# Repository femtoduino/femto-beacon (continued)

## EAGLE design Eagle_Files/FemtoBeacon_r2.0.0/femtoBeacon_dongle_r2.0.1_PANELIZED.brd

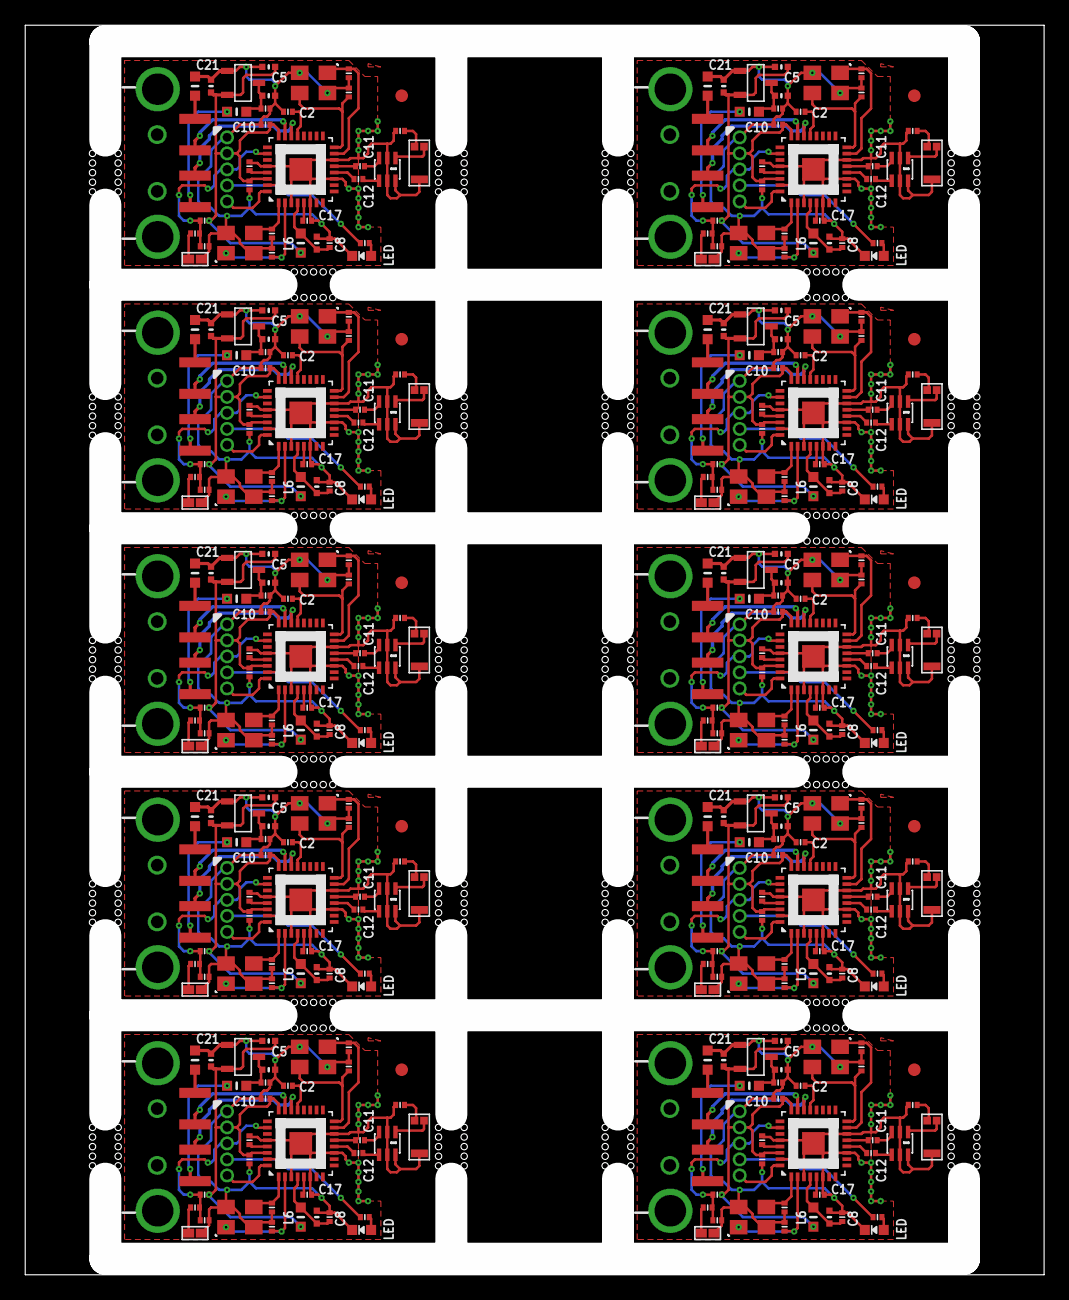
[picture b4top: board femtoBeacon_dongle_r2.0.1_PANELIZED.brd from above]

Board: 2 copper layers, 80.8 x 99.1 mm, 360 parts (0 on the bottom side), 260 nets.

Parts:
ANT1, ANT2, ANT3, ANT4, ANT5, ANT6, ANT7, ANT8, ANT9, ANT10: PULSE_ANT_2.4GHZ; ANT_BAR
BTN, BTN1, BTN2, BTN3, BTN4, BTN5, BTN6, BTN7, BTN8, BTN9: DNP; SPST_SMD
C1, C2, C8, C9, C10, C16, C17, C18, C19, C27, C28, C29, C37, C38, C39, C40, C46, C47, C48, C56, C57, C58, C59, C65, C66, C67, C75, C76, C77, C78, C84, C85, C86, C94, C95, C96, C97, C103, C104, C105, C113, C114, C115, C116, C122, C123, C124, C132, C133, C134, C135, C141, C142, C143, C151, C152, C153, C154, C160, C161, C162, C170, C171, C172, C173, C179, C180, C181, C189, C190: 0.1uF; PART
C3, C4, C32, C33, C51, C52, C70, C71, C89, C90, C108, C109, C127, C128, C146, C147, C165, C166, C184, C185: 10pF; PART
C5, C6, C34, C35, C53, C54, C72, C73, C91, C92, C110, C111, C129, C130, C148, C149, C167, C168, C186, C187: 2.2uF; _0402MP
C7, C36, C55, C74, C93, C112, C131, C150, C169, C188: 0.47uF; PART
C11, C12, C20, C23, C41, C42, C60, C61, C79, C80, C98, C99, C117, C118, C136, C137, C155, C156, C174, C175: 22pF, C0G, 5%; PART
C13, C24, C43, C62, C81, C100, C119, C138, C157, C176: DNP; PART
C14, C15, C25, C26, C44, C45, C63, C64, C82, C83, C101, C102, C120, C121, C139, C140, C158, C159, C177, C178: 9pF; PART
C21, C22, C30, C31, C49, C50, C68, C69, C87, C88, C106, C107, C125, C126, C144, C145, C163, C164, C182, C183: 10uF; _0402MP
CN1, CN2, CN3, CN4, CN5, CN6, CN7, CN8, CN9, CN10: USB_A-SMT
FB1, FB2, FB3, FB4, FB5, FB6, FB7, FB8, FB9, FB10, FB11, FB12, FB13, FB14, FB15, FB16, FB17, FB18, FB19, FB20: _0603MP
FID1, FID2, FID3, FID4, FID5, FID6, FID7, FID8, FID9, FID10: FIDUCIAL; FIDUCIAL_1MM
L1, L2, L3, L4, L5, L6, L7, L8, L9, L10: 10uH; _0603MP
LDO_VREG, LDO_VREG1, LDO_VREG2, LDO_VREG3, LDO_VREG4, LDO_VREG5, LDO_VREG6, LDO_VREG7, LDO_VREG8, LDO_VREG9: MCP1700T-3302E/TT
LED, LED1, LED2, LED3, LED4, LED5, LED6, LED7, LED8, LED9: BLUE; CHIPLED_0603_NOOUTLINE
R1, R3, R4, R6, R7, R9, R10, R12, R13, R15, R16, R18, R19, R21, R22, R24, R25, R27, R28, R30: 330; PART
R2, R5, R8, R11, R14, R17, R20, R23, R26, R29: 10K; PART
U$1, U$4, U$7, U$10, U$14, U$17, U$20, U$23, U$26, U$29: 1X5_ROUND
U$2, U$5, U$8, U$11, U$12, U$15, U$18, U$21, U$24, U$27: JOHANSON_2450BM15A0015E; 0805_BALUN
U$3, U$6, U$9, U$13, U$16, U$19, U$22, U$25, U$28, U$76: ATSAMR21E18A-MUT; QFN32
XOSC, XOSC1, XOSC2, XOSC3, XOSC4, XOSC5, XOSC6, XOSC7, XOSC8, XOSC9: 12MHz; TSX-3225
XOSCRF, XOSCRF1, XOSCRF2, XOSCRF3, XOSCRF4, XOSCRF5, XOSCRF6, XOSCRF7, XOSCRF8, XOSCRF9: 16MHz; TSX-3225

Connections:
3.3V: C5.1, C10.1, C16.1, C21.2, L6.1, LDO_VREG.VOUT, R2.2, U$1.P$2, U$76.24, U$76.30
3.3V1: C19.1, C27.1, C30.2, C34.1, L1.1, LDO_VREG1.VOUT, R5.2, U$3.24, U$3.30, U$4.P$2
3.3V2: C40.1, C46.1, C49.2, C53.1, L2.1, LDO_VREG2.VOUT, R8.2, U$6.24, U$6.30, U$7.P$2
3.3V3: C59.1, C65.1, C68.2, C72.1, L3.1, LDO_VREG3.VOUT, R11.2, U$9.24, U$9.30, U$10.P$2
3.3V4: C78.1, C84.1, C87.2, C91.1, L4.1, LDO_VREG4.VOUT, R14.2, U$13.24, U$13.30, U$14.P$2
3.3V5: C97.1, C103.1, C106.2, C110.1, L5.1, LDO_VREG5.VOUT, R17.2, U$16.24, U$16.30, U$17.P$2
3.3V6: C116.1, C122.1, C125.2, C129.1, L7.1, LDO_VREG6.VOUT, R20.2, U$19.24, U$19.30, U$20.P$2
3.3V7: C135.1, C141.1, C144.2, C148.1, L8.1, LDO_VREG7.VOUT, R23.2, U$22.24, U$22.30, U$23.P$2
3.3V8: C154.1, C160.1, C163.2, C167.1, L9.1, LDO_VREG8.VOUT, R26.2, U$25.24, U$25.30, U$26.P$2
3.3V9: C173.1, C179.1, C182.2, C186.1, L10.1, LDO_VREG9.VOUT, R29.2, U$28.24, U$28.30, U$29.P$2
ANT_OUT: ANT1.1, U$12.1
ANT_OUT1: ANT2.1, U$2.1
ANT_OUT2: ANT3.1, U$5.1
ANT_OUT3: ANT4.1, U$8.1
ANT_OUT4: ANT5.1, U$11.1
ANT_OUT5: ANT6.1, U$15.1
ANT_OUT6: ANT7.1, U$18.1
ANT_OUT7: ANT8.1, U$21.1
ANT_OUT8: ANT9.1, U$24.1
ANT_OUT9: ANT10.1, U$27.1
AVDD: C17.1, U$76.5
AVDD1: C28.1, U$3.5
AVDD2: C47.1, U$6.5
AVDD3: C66.1, U$9.5
AVDD4: C85.1, U$13.5
AVDD5: C104.1, U$16.5
AVDD6: C123.1, U$19.5
AVDD7: C142.1, U$22.5
AVDD8: C161.1, U$25.5
AVDD9: C180.1, U$28.5
DVDD: C2.1, U$76.21
DVDD1: C29.1, U$3.21
DVDD2: C48.1, U$6.21
DVDD3: C67.1, U$9.21
DVDD4: C86.1, U$13.21
DVDD5: C105.1, U$16.21
DVDD6: C124.1, U$19.21
DVDD7: C143.1, U$22.21
DVDD8: C162.1, U$25.21
DVDD9: C181.1, U$28.21
GND: ANT1.3, BTN.2, C1.2, C2.2, C3.1, C4.2, C5.2, C6.2, C7.2, C8.2, C9.2, C10.2, C13.2, C14.1, C15.2, C16.2, C17.2, C21.1, C22.1, FB1.2, LDO_VREG.GND, LED.C, U$1.P$1, U$12.2, U$12.5, U$12.6, U$76.3, U$76.6, U$76.11, U$76.14, U$76.28, U$76.33, XOSC.2, XOSC.4, XOSCRF.2, XOSCRF.4
GND1: ANT2.3, BTN1.2, C18.2, C19.2, C24.2, C25.1, C26.2, C27.2, C28.2, C29.2, C30.1, C31.1, C32.1, C33.2, C34.2, C35.2, C36.2, C37.2, C38.2, FB3.2, LDO_VREG1.GND, LED1.C, U$2.2, U$2.5, U$2.6, U$3.3, U$3.6, U$3.11, U$3.14, U$3.28, U$3.33, U$4.P$1, XOSC1.2, XOSC1.4, XOSCRF1.2, XOSCRF1.4
GND2: ANT3.3, BTN2.2, C39.2, C40.2, C43.2, C44.1, C45.2, C46.2, C47.2, C48.2, C49.1, C50.1, C51.1, C52.2, C53.2, C54.2, C55.2, C56.2, C57.2, FB5.2, LDO_VREG2.GND, LED2.C, U$5.2, U$5.5, U$5.6, U$6.3, U$6.6, U$6.11, U$6.14, U$6.28, U$6.33, U$7.P$1, XOSC2.2, XOSC2.4, XOSCRF2.2, XOSCRF2.4
GND3: ANT4.3, BTN3.2, C58.2, C59.2, C62.2, C63.1, C64.2, C65.2, C66.2, C67.2, C68.1, C69.1, C70.1, C71.2, C72.2, C73.2, C74.2, C75.2, C76.2, FB7.2, LDO_VREG3.GND, LED3.C, U$8.2, U$8.5, U$8.6, U$9.3, U$9.6, U$9.11, U$9.14, U$9.28, U$9.33, U$10.P$1, XOSC3.2, XOSC3.4, XOSCRF3.2, XOSCRF3.4
GND4: ANT5.3, BTN4.2, C77.2, C78.2, C81.2, C82.1, C83.2, C84.2, C85.2, C86.2, C87.1, C88.1, C89.1, C90.2, C91.2, C92.2, C93.2, C94.2, C95.2, FB9.2, LDO_VREG4.GND, LED4.C, U$11.2, U$11.5, U$11.6, U$13.3, U$13.6, U$13.11, U$13.14, U$13.28, U$13.33, U$14.P$1, XOSC4.2, XOSC4.4, XOSCRF4.2, XOSCRF4.4
GND5: ANT6.3, BTN5.2, C96.2, C97.2, C100.2, C101.1, C102.2, C103.2, C104.2, C105.2, C106.1, C107.1, C108.1, C109.2, C110.2, C111.2, C112.2, C113.2, C114.2, FB11.2, LDO_VREG5.GND, LED5.C, U$15.2, U$15.5, U$15.6, U$16.3, U$16.6, U$16.11, U$16.14, U$16.28, U$16.33, U$17.P$1, XOSC5.2, XOSC5.4, XOSCRF5.2, XOSCRF5.4
GND6: ANT7.3, BTN6.2, C115.2, C116.2, C119.2, C120.1, C121.2, C122.2, C123.2, C124.2, C125.1, C126.1, C127.1, C128.2, C129.2, C130.2, C131.2, C132.2, C133.2, FB13.2, LDO_VREG6.GND, LED6.C, U$18.2, U$18.5, U$18.6, U$19.3, U$19.6, U$19.11, U$19.14, U$19.28, U$19.33, U$20.P$1, XOSC6.2, XOSC6.4, XOSCRF6.2, XOSCRF6.4
GND7: ANT8.3, BTN7.2, C134.2, C135.2, C138.2, C139.1, C140.2, C141.2, C142.2, C143.2, C144.1, C145.1, C146.1, C147.2, C148.2, C149.2, C150.2, C151.2, C152.2, FB15.2, LDO_VREG7.GND, LED7.C, U$21.2, U$21.5, U$21.6, U$22.3, U$22.6, U$22.11, U$22.14, U$22.28, U$22.33, U$23.P$1, XOSC7.2, XOSC7.4, XOSCRF7.2, XOSCRF7.4
GND8: ANT9.3, BTN8.2, C153.2, C154.2, C157.2, C158.1, C159.2, C160.2, C161.2, C162.2, C163.1, C164.1, C165.1, C166.2, C167.2, C168.2, C169.2, C170.2, C171.2, FB17.2, LDO_VREG8.GND, LED8.C, U$24.2, U$24.5, U$24.6, U$25.3, U$25.6, U$25.11, U$25.14, U$25.28, U$25.33, U$26.P$1, XOSC8.2, XOSC8.4, XOSCRF8.2, XOSCRF8.4
GND9: ANT10.3, BTN9.2, C172.2, C173.2, C176.2, C177.1, C178.2, C179.2, C180.2, C181.2, C182.1, C183.1, C184.1, C185.2, C186.2, C187.2, C188.2, C189.2, C190.2, FB19.2, LDO_VREG9.GND, LED9.C, U$27.2, U$27.5, U$27.6, U$28.3, U$28.6, U$28.11, U$28.14, U$28.28, U$28.33, U$29.P$1, XOSC9.2, XOSC9.4, XOSCRF9.2, XOSCRF9.4
unnamed: C11.2, U$12.3
unnamed: ANT1.2, C13.1
unnamed: C12.2, U$12.4
unnamed: CN1.VBUS, FB2.1
unnamed: CN1.GND, FB1.1
unnamed: BTN1.1, R3.1
unnamed: LED1.A, R6.2
unnamed: C20.2, U$2.3
unnamed: LED.A, R4.2
unnamed: C23.2, U$2.4
unnamed: ANT2.2, C24.1
unnamed: CN2.GND, FB3.1
unnamed: CN2.VBUS, FB4.1
unnamed: BTN2.1, R7.1
unnamed: LED2.A, R9.2
unnamed: C41.2, U$5.3
unnamed: C42.2, U$5.4
unnamed: BTN.1, R1.1
unnamed: ANT3.2, C43.1
unnamed: CN3.GND, FB5.1
unnamed: CN3.VBUS, FB6.1
unnamed: BTN3.1, R10.1
unnamed: LED3.A, R12.2
unnamed: C60.2, U$8.3
unnamed: C61.2, U$8.4
unnamed: ANT4.2, C62.1
unnamed: CN4.GND, FB7.1
unnamed: CN4.VBUS, FB8.1
unnamed: BTN4.1, R13.1
unnamed: LED4.A, R15.2
unnamed: C79.2, U$11.3
unnamed: C80.2, U$11.4
unnamed: ANT5.2, C81.1
unnamed: CN5.GND, FB9.1
unnamed: CN5.VBUS, FB10.1
unnamed: BTN5.1, R16.1
unnamed: LED5.A, R18.2
unnamed: C98.2, U$15.3
unnamed: C99.2, U$15.4
unnamed: ANT6.2, C100.1
unnamed: CN6.GND, FB11.1
unnamed: CN6.VBUS, FB12.1
unnamed: BTN6.1, R19.1
unnamed: LED6.A, R21.2
unnamed: C117.2, U$18.3
unnamed: C118.2, U$18.4
unnamed: ANT7.2, C119.1
unnamed: CN7.GND, FB13.1
unnamed: CN7.VBUS, FB14.1
unnamed: BTN7.1, R22.1
unnamed: LED7.A, R24.2
unnamed: C136.2, U$21.3
unnamed: C137.2, U$21.4
unnamed: ANT8.2, C138.1
unnamed: CN8.GND, FB15.1
unnamed: CN8.VBUS, FB16.1
unnamed: BTN8.1, R25.1
unnamed: LED8.A, R27.2
unnamed: C155.2, U$24.3
unnamed: C156.2, U$24.4
unnamed: ANT9.2, C157.1
unnamed: CN9.GND, FB17.1
unnamed: CN9.VBUS, FB18.1
unnamed: BTN9.1, R28.1
unnamed: LED9.A, R30.2
unnamed: C174.2, U$27.3
unnamed: C175.2, U$27.4
unnamed: ANT10.2, C176.1
unnamed: CN10.GND, FB19.1
unnamed: CN10.VBUS, FB20.1
PA14/XIN_MC/RX: C3.2, U$76.15, XOSC.1
PA14/XIN_MC/RX1: C32.2, U$3.15, XOSC1.1
PA14/XIN_MC/RX2: C51.2, U$6.15, XOSC2.1
PA14/XIN_MC/RX3: C70.2, U$9.15, XOSC3.1
PA14/XIN_MC/RX4: C89.2, U$13.15, XOSC4.1
PA14/XIN_MC/RX5: C108.2, U$16.15, XOSC5.1
PA14/XIN_MC/RX6: C127.2, U$19.15, XOSC6.1
PA14/XIN_MC/RX7: C146.2, U$22.15, XOSC7.1
PA14/XIN_MC/RX8: C165.2, U$25.15, XOSC8.1
PA14/XIN_MC/RX9: C184.2, U$28.15, XOSC9.1
PA15/XOUT_MC/TX: C4.1, U$76.16, XOSC.3
PA15/XOUT_MC/TX1: C33.1, U$3.16, XOSC1.3
PA15/XOUT_MC/TX2: C52.1, U$6.16, XOSC2.3
PA15/XOUT_MC/TX3: C71.1, U$9.16, XOSC3.3
PA15/XOUT_MC/TX4: C90.1, U$13.16, XOSC4.3
PA15/XOUT_MC/TX5: C109.1, U$16.16, XOSC5.3
PA15/XOUT_MC/TX6: C128.1, U$19.16, XOSC6.3
PA15/XOUT_MC/TX7: C147.1, U$22.16, XOSC7.3
PA15/XOUT_MC/TX8: C166.1, U$25.16, XOSC8.3
PA15/XOUT_MC/TX9: C185.1, U$28.16, XOSC9.3
PA24/USBDM: CN1.D-, U$76.22
PA24/USBDM1: CN2.D-, U$3.22
PA24/USBDM2: CN3.D-, U$6.22
PA24/USBDM3: CN4.D-, U$9.22
PA24/USBDM4: CN5.D-, U$13.22
PA24/USBDM5: CN6.D-, U$16.22
PA24/USBDM6: CN7.D-, U$19.22
PA24/USBDM7: CN8.D-, U$22.22
PA24/USBDM8: CN9.D-, U$25.22
PA24/USBDM9: CN10.D-, U$28.22
PA25/USBDP: CN1.D+, U$76.23
PA25/USBDP1: CN2.D+, U$3.23
PA25/USBDP2: CN3.D+, U$6.23
PA25/USBDP3: CN4.D+, U$9.23
PA25/USBDP4: CN5.D+, U$13.23
PA25/USBDP5: CN6.D+, U$16.23
PA25/USBDP6: CN7.D+, U$19.23
PA25/USBDP7: CN8.D+, U$22.23
PA25/USBDP8: CN9.D+, U$25.23
PA25/USBDP9: CN10.D+, U$28.23
PA30/SWCLK: R4.1, U$1.P$4, U$76.31
PA30/SWCLK1: R6.1, U$3.31, U$4.P$4
PA30/SWCLK2: R9.1, U$6.31, U$7.P$4
PA30/SWCLK3: R12.1, U$9.31, U$10.P$4
PA30/SWCLK4: R15.1, U$13.31, U$14.P$4
PA30/SWCLK5: R18.1, U$16.31, U$17.P$4
PA30/SWCLK6: R21.1, U$19.31, U$20.P$4
PA30/SWCLK7: R24.1, U$22.31, U$23.P$4
PA30/SWCLK8: R27.1, U$25.31, U$26.P$4
PA30/SWCLK9: R30.1, U$28.31, U$29.P$4
PA31/SWDIO: U$1.P$5, U$76.32
PA31/SWDIO1: U$3.32, U$4.P$5
PA31/SWDIO2: U$6.32, U$7.P$5
PA31/SWDIO3: U$9.32, U$10.P$5
PA31/SWDIO4: U$13.32, U$14.P$5
PA31/SWDIO5: U$16.32, U$17.P$5
PA31/SWDIO6: U$19.32, U$20.P$5
PA31/SWDIO7: U$22.32, U$23.P$5
PA31/SWDIO8: U$25.32, U$26.P$5
PA31/SWDIO9: U$28.32, U$29.P$5
RESET: C1.1, R1.2, R2.1, U$1.P$3, U$76.26
RESET1: C18.1, R3.2, R5.1, U$3.26, U$4.P$3
RESET2: C39.1, R7.2, R8.1, U$6.26, U$7.P$3
RESET3: C58.1, R10.2, R11.1, U$9.26, U$10.P$3
RESET4: C77.1, R13.2, R14.1, U$13.26, U$14.P$3
RESET5: C96.1, R16.2, R17.1, U$16.26, U$17.P$3
RESET6: C115.1, R19.2, R20.1, U$19.26, U$20.P$3
RESET7: C134.1, R22.2, R23.1, U$22.26, U$23.P$3
RESET8: C153.1, R25.2, R26.1, U$25.26, U$26.P$3
RESET9: C172.1, R28.2, R29.1, U$28.26, U$29.P$3
RFN: C11.1, U$76.13
RFN1: C20.1, U$3.13
RFN2: C41.1, U$6.13
RFN3: C60.1, U$9.13
RFN4: C79.1, U$13.13
RFN5: C98.1, U$16.13
RFN6: C117.1, U$19.13
RFN7: C136.1, U$22.13
RFN8: C155.1, U$25.13
RFN9: C174.1, U$28.13
RFP: C12.1, U$76.12
RFP1: C23.1, U$3.12
RFP2: C42.1, U$6.12
RFP3: C61.1, U$9.12
RFP4: C80.1, U$13.12
RFP5: C99.1, U$16.12
RFP6: C118.1, U$19.12
RFP7: C137.1, U$22.12
RFP8: C156.1, U$25.12
RFP9: C175.1, U$28.12
VDDANA: C8.1, C22.2, L6.2, U$76.4
VDDANA1: C31.2, C37.1, L1.2, U$3.4
VDDANA2: C50.2, C56.1, L2.2, U$6.4
VDDANA3: C69.2, C75.1, L3.2, U$9.4
VDDANA4: C88.2, C94.1, L4.2, U$13.4
VDDANA5: C107.2, C113.1, L5.2, U$16.4
VDDANA6: C126.2, C132.1, L7.2, U$19.4
VDDANA7: C145.2, C151.1, L8.2, U$22.4
VDDANA8: C164.2, C170.1, L9.2, U$25.4
VDDANA9: C183.2, C189.1, L10.2, U$28.4
VDDCORE: C9.1, U$76.29
VDDCORE1: C38.1, U$3.29
VDDCORE2: C57.1, U$6.29
VDDCORE3: C76.1, U$9.29
VDDCORE4: C95.1, U$13.29
VDDCORE5: C114.1, U$16.29
VDDCORE6: C133.1, U$19.29
VDDCORE7: C152.1, U$22.29
VDDCORE8: C171.1, U$25.29
VDDCORE9: C190.1, U$28.29
VIN: C6.1, C7.1, FB2.2, LDO_VREG.VIN
VIN1: C35.1, C36.1, FB4.2, LDO_VREG1.VIN
VIN2: C54.1, C55.1, FB6.2, LDO_VREG2.VIN
VIN3: C73.1, C74.1, FB8.2, LDO_VREG3.VIN
VIN4: C92.1, C93.1, FB10.2, LDO_VREG4.VIN
VIN5: C111.1, C112.1, FB12.2, LDO_VREG5.VIN
VIN6: C130.1, C131.1, FB14.2, LDO_VREG6.VIN
VIN7: C149.1, C150.1, FB16.2, LDO_VREG7.VIN
VIN8: C168.1, C169.1, FB18.2, LDO_VREG8.VIN
VIN9: C187.1, C188.1, FB20.2, LDO_VREG9.VIN
XTALIN: C14.2, U$76.2, XOSCRF.1
XTALIN1: C25.2, U$3.2, XOSCRF1.1
XTALIN2: C44.2, U$6.2, XOSCRF2.1
XTALIN3: C63.2, U$9.2, XOSCRF3.1
XTALIN4: C82.2, U$13.2, XOSCRF4.1
XTALIN5: C101.2, U$16.2, XOSCRF5.1
XTALIN6: C120.2, U$19.2, XOSCRF6.1
XTALIN7: C139.2, U$22.2, XOSCRF7.1
XTALIN8: C158.2, U$25.2, XOSCRF8.1
XTALIN9: C177.2, U$28.2, XOSCRF9.1
XTALOUT: C15.1, U$76.1, XOSCRF.3
XTALOUT1: C26.1, U$3.1, XOSCRF1.3
XTALOUT2: C45.1, U$6.1, XOSCRF2.3
XTALOUT3: C64.1, U$9.1, XOSCRF3.3
XTALOUT4: C83.1, U$13.1, XOSCRF4.3
XTALOUT5: C102.1, U$16.1, XOSCRF5.3
XTALOUT6: C121.1, U$19.1, XOSCRF6.3
XTALOUT7: C140.1, U$22.1, XOSCRF7.3
XTALOUT8: C159.1, U$25.1, XOSCRF8.3
XTALOUT9: C178.1, U$28.1, XOSCRF9.3

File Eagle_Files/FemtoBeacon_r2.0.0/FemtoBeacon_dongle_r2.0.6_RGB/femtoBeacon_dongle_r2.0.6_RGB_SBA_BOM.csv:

##########################################################################
       Name: Placement Bill of Materials Generator

    Version: 4 (2-sided, top)
         By: Small Batch Assembly
        URL: www.smallbatchassembly.com
 SourceFile: femtoBeacon_dongle_r2.0.6_RGB.brd
   DateTime: 1/3/18 4:22 AM
      Units: inches
##########################################################################
REF,PACKAGE,VALUE,X,Y,ROTATION,
ASWITCH   , AS222-92LF            , AS222-92LF     , 1.1500, 0.5100, 0.0
BTN   , SPST_SMD            , DNP     , 0.4800, 0.2300, 0.0
C1   , PART            , 0.1uF     , 0.5100, 0.2700, 0.0
C2   , PART            , 0.1uF     , 0.7700, 0.6900, 180.0
C5   , _0402MP            , 2.2uF     , 0.7100, 0.8300, 180.0
C6   , _0402MP            , 2.2uF     , 0.7100, 0.7400, 0.0
C7   , PART            , 0.47uF     , 0.7000, 0.7000, 0.0
C8   , PART            , 0.1uF     , 0.9000, 0.2800, 90.0
C9   , PART            , 0.1uF     , 0.6500, 0.5200, 90.0
C10   , PART            , 0.1uF     , 0.7000, 0.6500, 180.0
C11   , _0402MP            , 1.2pF     , 1.2300, 0.6000, 180.0
C13   , PART            , DNP     , 1.1100, 0.6600, 180.0
C14   , PART            , 9pF     , 0.7200, 0.2500, 270.0
C15   , PART            , 9pF     , 0.7200, 0.3100, 270.0
C16   , PART            , 0.1uF     , 0.6500, 0.4600, 270.0
C17   , PART            , 0.1uF     , 0.8300, 0.3500, 0.0
C18   , PART            , 22pF     , 1.1500, 0.5900, 270.0
C19   , PART            , 22pF     , 1.1800, 0.5900, 270.0
C20   , PART            , 22pF     , 1.1200, 0.5900, 90.0
C21   , _0402MP            , 10uF     , 0.5300, 0.7700, 270.0
C22   , _0402MP            , 10uF     , 0.8600, 0.2800, 270.0
C23   , PART            , 22pF     , 1.1760, 0.3980, 90.0
C24   , PART            , 22pF     , 1.2400, 0.5400, 90.0
CN1   , USB_A-SMT            ,      , 0.4800, 0.5300, 90.0
FB1   , _0603MP            ,      , 0.4800, 0.7700, 90.0
FB2   , _0603MP            ,      , 0.6100, 0.6900, 0.0
FID1   , FIDUCIAL_1MM            , FIDUCIAL     , 0.1000, 0.3000, 0.0
FID2   , FIDUCIAL_1MM            , FIDUCIAL     , 0.1000, 0.8000, 0.0
FID3   , FIDUCIAL_1MM            , FIDUCIAL     , 1.4500, 0.8000, 0.0
L1   , _0603MP            , 1.8nH     , 1.2060, 0.6560, 0.0
L6   , _0603MP            , 10uH     , 0.8100, 0.2800, 90.0
LDO_VREG   , MCP1700T-3302E/TT            , MCP1700T-3302E/TT     , 0.6300, 0.7800, 270.0
R1   , PART            , 330     , 0.4800, 0.3100, 0.0
R2   , PART            , 10K     , 0.5100, 0.3500, 0.0
R4   , PART            , 330     , 0.9700, 0.2600, 0.0
R6   , PART            , 330     , 0.9700, 0.3000, 0.0
R7   , PART            , 330     , 0.9800, 0.3480, 0.0
RGBLED   , LRTB_R48G            , LRTB_R48G     , 1.0300, 0.2800, 270.0
U$6   , 0479480001            , 0479480001     , 1.2040, 0.7770, 90.0
U$12   , 0805_BALUN            , JOHANSON_2450BM15A0015E     , 1.0500, 0.5100, 270.0
U$76   , QFN32            , ATSAMR21E18A-MUT     , 0.8100, 0.5100, 90.0
UFLANT   , U.FL            , uFL     , 1.1860, 0.2900, 90.0
XOSCRF   , TSX-3225            , 16MHz     , 0.6200, 0.2800, 0.0
